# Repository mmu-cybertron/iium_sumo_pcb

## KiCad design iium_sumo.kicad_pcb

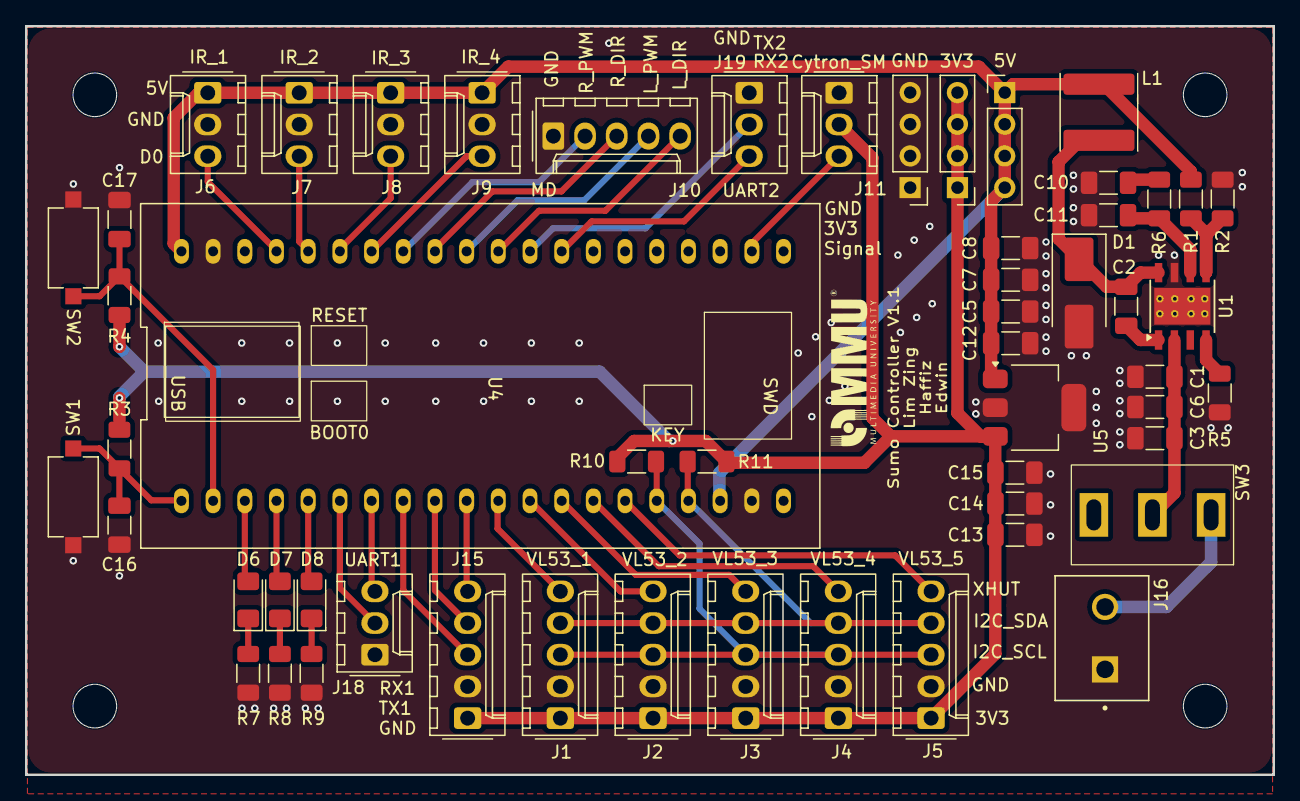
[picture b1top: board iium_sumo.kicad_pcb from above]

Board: 2 copper layers, 100.0 x 60.0 mm, 56 parts (1 on the bottom side), 42 nets.

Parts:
C1, C5, C6, C7: 22u; C_1206_3216Metric_Pad1.33x1.80mm_HandSolder
C2: 0.1u; C_1206_3216Metric_Pad1.33x1.80mm_HandSolder
C3, C8, C12, C13: 47u; C_1206_3216Metric_Pad1.33x1.80mm_HandSolder
C10: 1500p; C_1206_3216Metric_Pad1.33x1.80mm_HandSolder
C11: 47p; C_1206_3216Metric_Pad1.33x1.80mm_HandSolder
C14: 0.01u; C_1206_3216Metric_Pad1.33x1.80mm_HandSolder
C15: 1u; C_1206_3216Metric_Pad1.33x1.80mm_HandSolder
C16, C17: 100n; C_1206_3216Metric_Pad1.33x1.80mm_HandSolder
D1: Schottky SS54; D_SMB_Handsoldering
D6, D7, D8: LED; LED_1206_3216Metric_Pad1.42x1.75mm_HandSolder
J1: I2C_VL53_1; Molex_KK-254_AE-6410-05A_1x05_P2.54mm_Vertical
J2: I2C_VL53_2; Molex_KK-254_AE-6410-05A_1x05_P2.54mm_Vertical
J3: I2C_VL53_3; Molex_KK-254_AE-6410-05A_1x05_P2.54mm_Vertical
J4: I2C_VL53_4; Molex_KK-254_AE-6410-05A_1x05_P2.54mm_Vertical
J5: I2C_VL53_5; Molex_KK-254_AE-6410-05A_1x05_P2.54mm_Vertical
J6: IR_1; Molex_KK-254_AE-6410-03A_1x03_P2.54mm_Vertical
J7: IR_2; Molex_KK-254_AE-6410-03A_1x03_P2.54mm_Vertical
J8: IR_3; Molex_KK-254_AE-6410-03A_1x03_P2.54mm_Vertical
J9: IR_4; Molex_KK-254_AE-6410-03A_1x03_P2.54mm_Vertical
J10: Cytron MD; Molex_KK-254_AE-6410-05A_1x05_P2.54mm_Vertical
J11: Cytron Start Module; Molex_KK-254_AE-6410-03A_1x03_P2.54mm_Vertical
J12, J13, J14: Conn_01x04; PinHeader_1x04_P2.54mm_Vertical
J15: EXTRA1; Molex_KK-254_AE-6410-05A_1x05_P2.54mm_Vertical
J16: Conn_01x02_Pin; HANDSON_KF301-2P
J17: Conn_01x02_Pin; Wire Solder Pad
J18: UART1; Molex_KK-254_AE-6410-03A_1x03_P2.54mm_Vertical
J19: UART2; Molex_KK-254_AE-6410-03A_1x03_P2.54mm_Vertical
L1: 15uH; L_Sunlord_SWPA6045S
R1: 43k; R_1206_3216Metric_Pad1.30x1.75mm_HandSolder
R2: 8.2k; R_1206_3216Metric_Pad1.30x1.75mm_HandSolder
R3, R4: 10k; R_1206_3216Metric_Pad1.30x1.75mm_HandSolder
R5: 150k; R_1206_3216Metric_Pad1.30x1.75mm_HandSolder
R6: 10K; R_1206_3216Metric_Pad1.30x1.75mm_HandSolder
R7, R8, R9: 3.9k; R_1206_3216Metric_Pad1.30x1.75mm_HandSolder
R10, R11: 4.7k; R_1206_3216Metric_Pad1.30x1.75mm_HandSolder
SW1, SW2: SW_SPST; push_button
SW3: SW_SPDT; SPDT_MT-1-102-A001-M200-RS
U1: TPS54360DDA; TI_SO-PowerPAD-8_ThermalVias
U4: Black Pill v2; Module_BlackPill_v2
U5: LM3940; SOT-223-3_TabPin2

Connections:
+3V3: C13.1, C14.1, C15.1, J1.1, J2.1, J3.1, J4.1, J5.1, J11.2, J12.1, J12.2, J12.3, J12.4, J15.1, R3.1, R4.1, R10.1, R11.1, U5.3 (VO)
+5V: C5.1, C7.1, C8.1, C12.1, J6.1, J7.1, J8.1, J9.1, J13.1, J13.2, J13.3, J13.4, L1.2, R1.1, U4.18 (+5V), U4.40 (5V), U5.1 (VI)
+36V: J16.2, J17.2, SW3.1 (A)
/I2C_SCL: J1.3, J2.3, J3.3, J4.3, J5.3, R10.2, U4.16 (PB8)
/I2C_SDA: J1.4, J2.4, J3.4, J4.4, J5.4, R11.2, U4.17 (PB9)
/IR1_D0: J6.3, U4.37 (PB10)
/IR2_D0: J7.3, U4.36 (PB2)
/IR3_D0: J8.3, U4.35 (PB1)
/IR4_D0: J9.3, U4.34 (PB0)
/LEFT_DIR: J10.5, U4.30 (PA4)
/LEFT_PWM: J10.4, U4.31 (PA5)
/PA8: D8.2 (A), U4.5 (PA8)
/PA11: J15.3, U4.8 (PA11)
/PA12: J15.4, U4.9 (PA12)
/PA15: J15.5, U4.10 (PA15)
/PB12: C16.1, R3.2, SW1.1 (A), U4.1 (PB12)
/PB13: C17.1, R4.2, SW2.1 (A), U4.2 (PB13)
/PB14: D6.2 (A), U4.3 (PB14)
/PB15: D7.2 (A), U4.4 (PB15)
/RIGHT_DIR: J10.3, U4.32 (PA6)
/RIGHT_PWM: J10.2, U4.33 (PA7)
/RX1: J18.3, U4.7 (PA10)
/RX2: J19.3, U4.28 (PA2)
/SM_Signal: J11.3, U4.22 (PC13)
/TX1: J18.2, U4.6 (PA9)
/TX2: J19.2, U4.29 (PA3)
/XHUT1: J1.5, U4.11 (PB3)
/XHUT2: J2.5, U4.12 (PB4)
/XHUT3: J3.5, U4.13 (PB5)
/XHUT4: J4.5, U4.14 (PB6)
/XHUT5: J5.5, U4.15 (PB7)
COMP: C11.1, R6.1, U1.6 (COMP)
FB: R1.2, R2.1, U1.5 (FB)
GND: C1.2, C3.2, C5.2, C6.2, C7.2, C8.2, C10.2, C11.2, C12.2, C13.2, C14.2, C15.2, C16.2, C17.2, D1.2 (A), J1.2, J2.2, J3.2, J4.2, J5.2, J6.2, J7.2, J8.2, J9.2, J10.1, J11.1, J14.1, J14.2, J14.3, J14.4, J15.2, J16.1, J17.1, J18.1, J19.1, R2.2, R5.2, R7.1, R8.1, R9.1, SW1.2 (B), SW2.2 (B), U1.7 (GND), U1.9 (GNDPAD), U4.19 (GND), U4.39 (GND), U5.2 (GND)
unnamed: C10.1, R6.2
unnamed: C2.2, D1.1 (K), L1.1, U1.8 (SW)
unnamed: D6.1 (K), R7.2
unnamed: D7.1 (K), R8.2
unnamed: D8.1 (K), R9.2
unnamed: C1.1, C3.1, C6.1, SW3.2 (B), U1.2 (VIN)
unnamed: C2.1, U1.1 (BOOT)
unnamed: R5.1, U1.4 (RT/CLK)

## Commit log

2026-05-31 Added Labels
2026-05-31 Updated pull resisto
2026-06-02 schematic update
2026-06-02 pcb update and rearrange
2026-06-02 touch up
2026-06-02 New fixes
2026-06-02 drc cleared
2026-06-02 relayout button
2026-06-30 Restructure repo and latest changes
